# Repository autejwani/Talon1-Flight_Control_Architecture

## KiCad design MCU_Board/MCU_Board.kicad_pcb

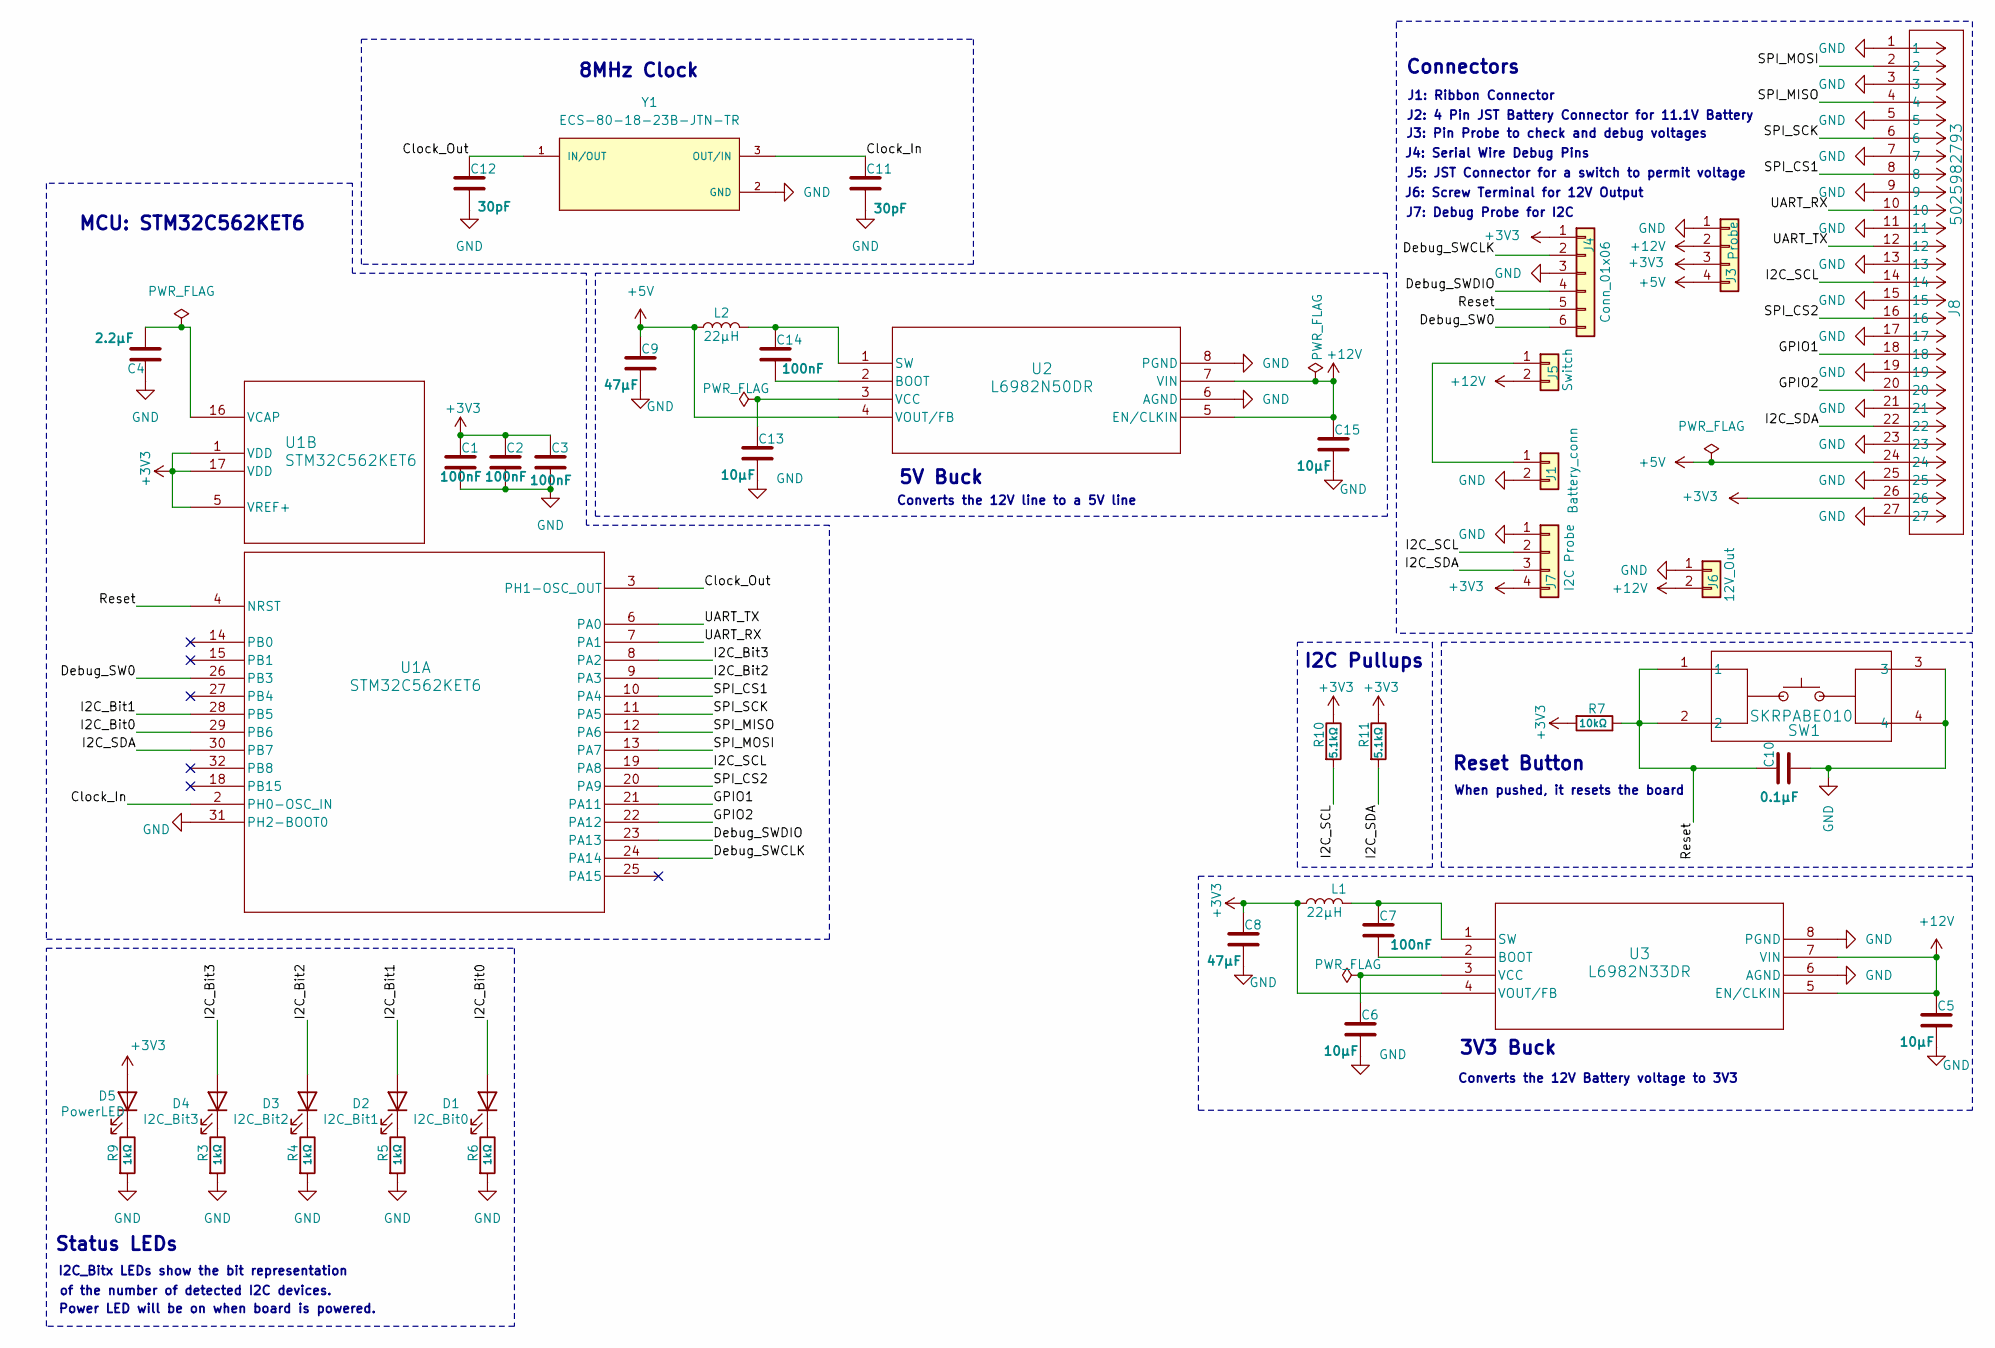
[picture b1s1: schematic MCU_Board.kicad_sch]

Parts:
C1, C2, C3, C7, C14: 100nF; C_0805_2012Metric
C4: 2.2μF; C_0805_2012Metric
C5, C6, C13, C15: 10μF; C_0805_2012Metric
C8, C9: 47μF; C_0805_2012Metric
C10: 0.1μF; C_0805_2012Metric
C11, C12: 30pF; C_0805_2012Metric
D1: I2C_Bit0; LED_0805_2012Metric
D2: I2C_Bit1; LED_0805_2012Metric
D3: I2C_Bit2; LED_0805_2012Metric
D4: I2C_Bit3; LED_0805_2012Metric
D5: PowerLED; LED_0805_2012Metric
J1: Battery_conn; TerminalBlock_MaiXu_MX126-5.0-02P_1x02_P5.00mm
J3: Probe; PinHeader_1x04_P1.00mm_Vertical
J4: Conn_01x06; PinHeader_1x06_P1.00mm_Vertical
J5: Switch; JST_EH_B2B-EH-A_1x02_P2.50mm_Vertical
J6: 12V_Out; TerminalBlock_MaiXu_MX126-5.0-02P_1x02_P5.00mm
J7: I2C Probe; PinHeader_1x04_P1.00mm_Vertical
J8: 5025982793; CONN_502598-2793_MOL
L1, L2: 22μH; L_0805_2012Metric
R3, R4, R5, R6, R9: 1kΩ; R_0603_1608Metric
R7: 10kΩ; R_0603_1608Metric
R10, R11: 5.1kΩ; R_0603_1608Metric
SW1: SKRPABE010; SW4_SKRPABE010_ALPS
U1: STM32C562KET6; LQFP-32_STM
U2: L6982N50DR; SO-8_STM
U3: L6982N33DR; SO-8_STM
Y1: ECS-80-18-23B-JTN-TR; XTAL_ECS-80-18-23B-JTN-TR; DigiKey_Part_Number XC3083CT-ND

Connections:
+3V3: C1.1, C2.1, C3.1, C8.1, D5.2 (A), J3.3, J4.1, J7.4, J8.26, L1.1, R7.2, R10.1, R11.1, U1.1 (VDD), U1.5 (VREF+), U1.17 (VDD), U3.4 (VOUT/FB)
+5V: C9.1, J3.4, J8.24, L2.1, U2.4 (VOUT/FB)
+12V: C5.1, C15.1, J3.2, J5.2, J6.2, U2.5 (EN/CLKIN), U2.7 (VIN), U3.5 (EN/CLKIN), U3.7 (VIN)
/Clock_In: C11.1, U1.2 (PH0-OSC_IN), Y1.3 (OUT/IN)
/Clock_Out: C12.1, U1.3 (PH1-OSC_OUT), Y1.1 (IN/OUT)
/Debug_SW0: J4.6, U1.26 (PB3)
/Debug_SWCLK: J4.2, U1.24 (PA14)
/Debug_SWDIO: J4.4, U1.23 (PA13)
/GPIO1: J8.18, U1.21 (PA11)
/GPIO2: J8.20, U1.22 (PA12)
/I2C_Bit0: D1.2 (A), U1.29 (PB6)
/I2C_Bit1: D2.2 (A), U1.28 (PB5)
/I2C_Bit2: D3.2 (A), U1.9 (PA3)
/I2C_Bit3: D4.2 (A), U1.8 (PA2)
/I2C_SCL: J7.2, J8.14, R10.2, U1.19 (PA8)
/I2C_SDA: J7.3, J8.22, R11.2, U1.30 (PB7)
/Reset: C10.1, J4.5, R7.1, SW1.1, SW1.2, U1.4 (NRST)
/SPI_CS1: J8.8, U1.10 (PA4)
/SPI_CS2: J8.16, U1.20 (PA9)
/SPI_MISO: J8.4, U1.12 (PA6)
/SPI_MOSI: J8.2, U1.13 (PA7)
/SPI_SCK: J8.6, U1.11 (PA5)
/UART_RX: J8.10, U1.7 (PA1)
/UART_TX: J8.12, U1.6 (PA0)
GND: C1.2, C2.2, C3.2, C4.1, C5.2, C6.2, C8.2, C9.2, C10.2, C11.2, C12.2, C13.2, C15.2, J1.2, J3.1, J4.3, J6.1, J7.1, J8.1, J8.3, J8.5, J8.7, J8.9, J8.11, J8.13, J8.15, J8.17, J8.19, J8.21, J8.23, J8.25, J8.27, R3.2, R4.2, R5.2, R6.2, R9.2, SW1.3, SW1.4, U1.31 (PH2-BOOT0), U2.6 (AGND), U2.8 (PGND), U3.6 (AGND), U3.8 (PGND), Y1.2 (GND), Y1.4 (GND)
unnamed: D1.1 (K), R6.1
unnamed: D2.1 (K), R5.1
unnamed: D3.1 (K), R4.1
unnamed: D4.1 (K), R3.1
unnamed: D5.1 (K), R9.1
unnamed: J1.1, J5.1
unnamed: C4.2, U1.16 (VCAP)
unnamed: C14.2, U2.2 (BOOT)
unnamed: C14.1, L2.2, U2.1 (SW)
unnamed: C13.1, U2.3 (VCC)
unnamed: C7.2, U3.2 (BOOT)
unnamed: C7.1, L1.2, U3.1 (SW)
unnamed: C6.1, U3.3 (VCC)

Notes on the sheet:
MCU: STM32C562KET6
J5: JST Connector for a switch to permit voltage
J3: Pin Probe to check and debug voltages
3V3 Buck
J4: Serial Wire Debug Pins
I2C_Bitx LEDs show the bit representation
of the number of detected I2C devices.
Status LEDs
5V Buck
8MHz Clock
Connectors
J2: 4 Pin JST Battery Connector for 11.1V Battery
J7: Debug Probe for I2C
Converts the 12V line to a 5V line
J6: Screw Terminal for 12V Output
I2C Pullups
When pushed, it resets the board
Reset Button
J1: Ribbon Connector
Power LED will be on when board is powered.
Converts the 12V Battery voltage to 3V3

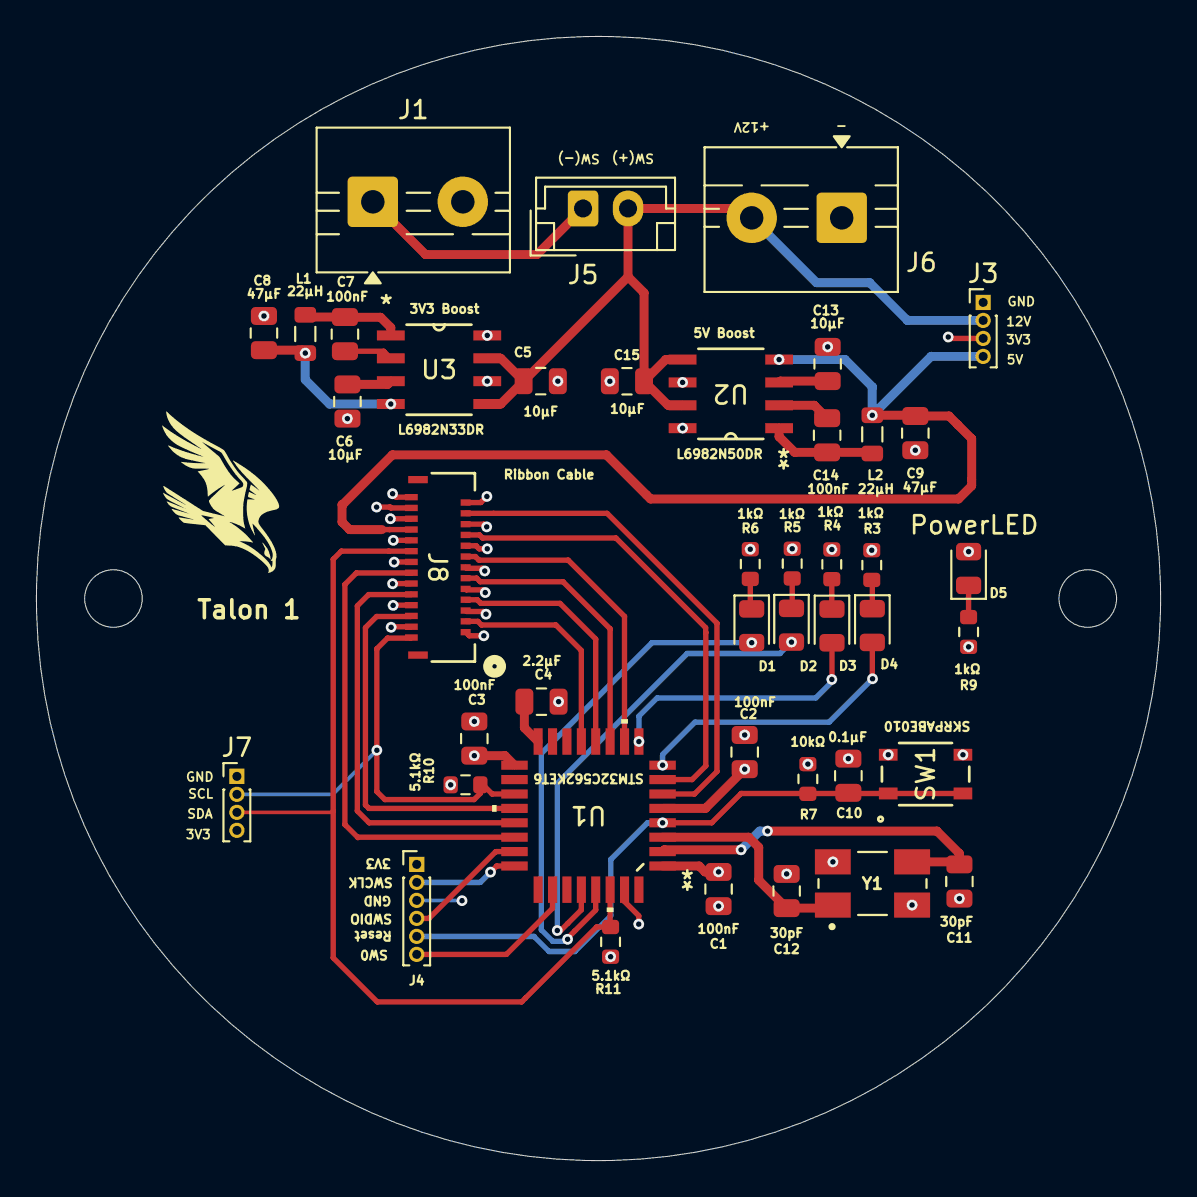
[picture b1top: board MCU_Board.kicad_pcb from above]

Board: 4 copper layers, 62.5 x 62.5 mm, 42 parts (0 on the bottom side), 38 nets.
